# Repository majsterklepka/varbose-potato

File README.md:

# varbose-potato
Digital Voltmeter based on ICL7107

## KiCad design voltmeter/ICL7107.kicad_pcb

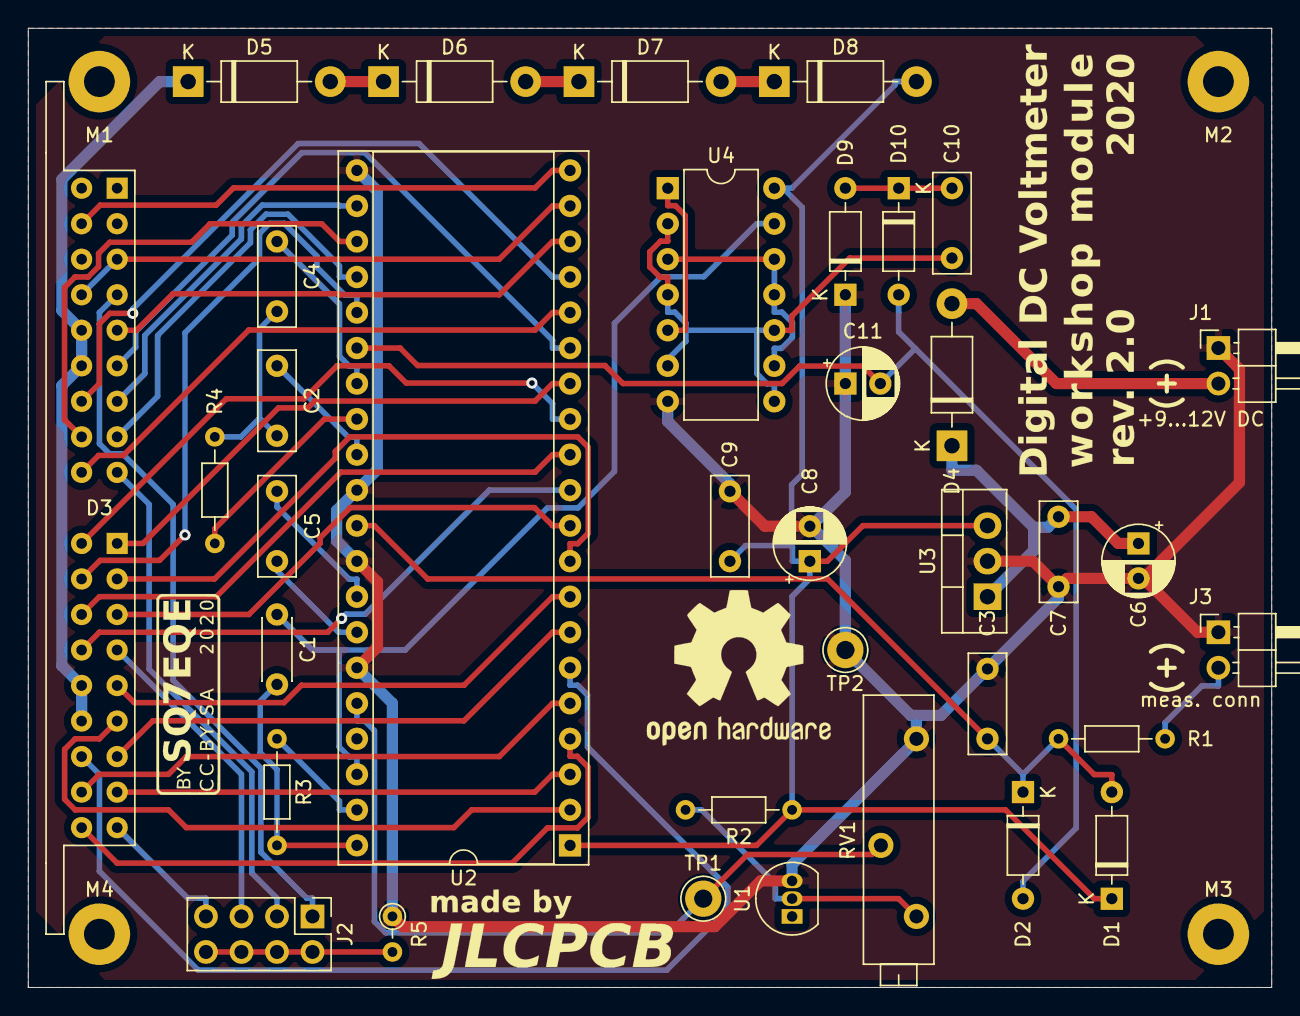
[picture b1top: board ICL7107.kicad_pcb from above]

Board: 2 copper layers, 88.9 x 68.6 mm, 43 parts (0 on the bottom side), 53 nets.

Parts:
C1: 100p; C_Disc_D4.3mm_W1.9mm_P5.00mm
C2, C3, C10: 0.47u; C_Rect_L7.0mm_W2.5mm_P5.00mm
C4: 0.22u; C_Rect_L7.0mm_W2.5mm_P5.00mm
C5: 0.1u; C_Rect_L7.0mm_W2.5mm_P5.00mm
C6, C8: 100u; CP_Radial_D5.0mm_P2.50mm
C7, C9: 100n; C_Rect_L7.0mm_W2.5mm_P5.00mm
C11: 10u; CP_Radial_D5.0mm_P2.50mm
D1, D2: 1N4148; D_DO-35_SOD27_P7.62mm_Horizontal
D3: LED-Display_x4_CA; LED-Display_x4_package
D4, D5, D6, D7, D8: 1N4001; D_DO-41_SOD81_P10.16mm_Horizontal
D9, D10: 1N914; D_DO-35_SOD27_P7.62mm_Horizontal
G1: CC-BY-SA; cc-by-sa
G2: JLCPCB; jlcpcb
J1: +9...12V DC; PinHeader_1x02_P2.54mm_Horizontal
J2: DP conn.; PinHeader_2x04_P2.54mm_Vertical
J3: meas. conn; PinHeader_1x02_P2.54mm_Horizontal
LOGO1: Logo_Open_Hardware_Large; OSHW-Logo2_14.6x12mm_SilkScreen
M1, M2, M3, M4: M2.2; MountingHole_2.2mm_M2_Pad
R1: 1M; R_Axial_DIN0204_L3.6mm_D1.6mm_P7.62mm_Horizontal
R2: 6k8; R_Axial_DIN0204_L3.6mm_D1.6mm_P7.62mm_Horizontal
R3: 100k; R_Axial_DIN0204_L3.6mm_D1.6mm_P7.62mm_Horizontal
R4: 47k; R_Axial_DIN0204_L3.6mm_D1.6mm_P7.62mm_Horizontal
R5: 470R; R_Axial_DIN0204_L3.6mm_D1.6mm_P2.54mm_Vertical
RV1: 20k; Potentiometer_Vishay_43_Horizontal
TP1, TP2: Pin_D1.3mm_L11.0mm
U1: LM285Z-1.2; TO-92_Inline
U2: ICL7107; DIP-40_W15.24mm_Socket
U3: L7805; TO-220-3_Vertical
U4: 4069; DIP-14_W7.62mm

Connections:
+5V: C8.1, C9.1, D1.1, D8.2, R2.1, U2.1, U3.3, U4.14
-5V: C11.2, D2.2, D10.2, U2.26
/DP1: D3.27, J2.7
/DP2: D3.22, J2.5
/DP3: D3.9, J2.3
/DP4: D3.4, J2.1
/IN+: J3.2, R1.2
GND: C3.2, C6.2, C7.2, C8.2, C9.2, C11.1, D9.1, J1.1, J3.1, R5.1, RV1.1, TP2.1, U1.3, U2.21, U2.30, U2.32, U2.35, U3.2, U4.7
unnamed: C1.2, R3.2, U2.40
unnamed: C2.1, U2.29
unnamed: C2.2, C4.2, R4.2
unnamed: C3.1, D1.2, D2.1, R1.1, U2.31
unnamed: C4.1, U2.27
unnamed: C5.1, U2.34
unnamed: C5.2, U2.33
unnamed: C6.1, C7.1, D4.1, U3.1
unnamed: C10.1, D9.2, D10.1
unnamed: C10.2, U4.2, U4.4, U4.6, U4.8, U4.10
unnamed: D3.5, U2.18
unnamed: D3.6, U2.15
unnamed: D3.7, U2.22
unnamed: D3.8, U2.24
unnamed: D3.10, U2.16
unnamed: D3.11, U2.23
unnamed: D3.12, U2.17
unnamed: D3.13, D3.14, D3.31, D3.32, D5.1
unnamed: D3.3, D3.15, U2.19
unnamed: D3.17, U2.20
unnamed: D3.19, U2.14
unnamed: D3.20, U2.9
unnamed: D3.21, U2.10
unnamed: D3.23, U2.8
unnamed: D3.24, U2.2
unnamed: D3.25, U2.7
unnamed: D3.26, U2.3
unnamed: D3.28, U2.4
unnamed: D3.29, U2.5
unnamed: D3.30, U2.6
unnamed: D3.33, U2.11
unnamed: D3.34, U2.12
unnamed: D3.35, U2.25
unnamed: D3.36, U2.13
unnamed: D4.2, J1.2
unnamed: D5.2, D6.1
unnamed: D6.2, D7.1
unnamed: D7.2, D8.1
unnamed: J2.2, J2.4, J2.6, J2.8, R5.2
unnamed: R2.2, RV1.3, U1.2
unnamed: R3.1, U2.39
unnamed: R4.1, U2.28
unnamed: RV1.2, TP1.1, U2.36
unnamed: U4.1, U4.3, U4.5, U4.9, U4.11, U4.12
OSC3: C1.1, U2.38, U4.13

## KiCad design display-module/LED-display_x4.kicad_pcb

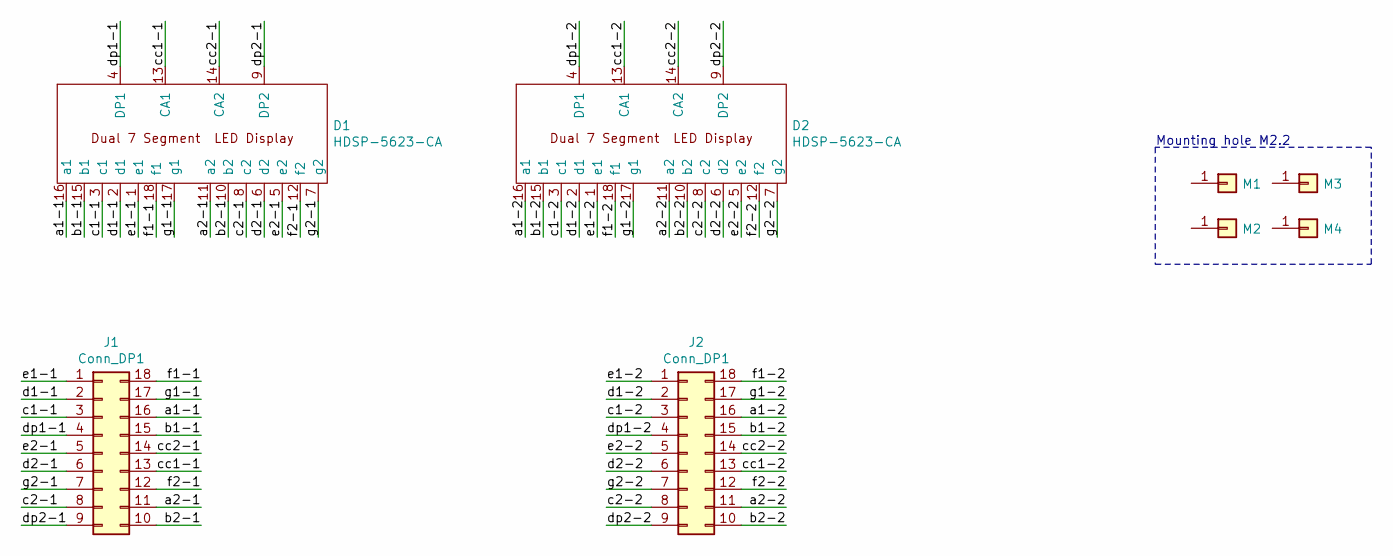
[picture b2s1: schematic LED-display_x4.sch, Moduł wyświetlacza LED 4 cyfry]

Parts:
D1, D2: HDSP-5623-CA; package_led_display_0.56in_dual
J1, J2: Conn_DP1; PinHeader_2x09_P2.54mm_Horizontal
M1, M2, M3, M4: Conn_01x01; MountingHole_2.2mm_M2

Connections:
/a1-1: D1.16 (a1), J1.16
/a1-2: D2.16 (a1), J2.16
/a2-1: D1.11 (a2), J1.11
/a2-2: D2.11 (a2), J2.11
/b1-1: D1.15 (b1), J1.15
/b1-2: D2.15 (b1), J2.15
/b2-1: D1.10 (b2), J1.10
/b2-2: D2.10 (b2), J2.10
/c1-1: D1.3 (c1), J1.3
/c1-2: D2.3 (c1), J2.3
/c2-1: D1.8 (c2), J1.8
/c2-2: D2.8 (c2), J2.8
/cc1-1: D1.13 (CA1), J1.13
/cc1-2: D2.13 (CA1), J2.13
/cc2-1: D1.14 (CA2), J1.14
/cc2-2: D2.14 (CA2), J2.14
/d1-1: D1.2 (d1), J1.2
/d1-2: D2.2 (d1), J2.2
/d2-1: D1.6 (d2), J1.6
/d2-2: D2.6 (d2), J2.6
/dp1-1: D1.4 (DP1), J1.4
/dp1-2: D2.4 (DP1), J2.4
/dp2-1: D1.9 (DP2), J1.9
/dp2-2: D2.9 (DP2), J2.9
/e1-1: D1.1 (e1), J1.1
/e1-2: D2.1 (e1), J2.1
/e2-1: D1.5 (e2), J1.5
/e2-2: D2.5 (e2), J2.5
/f1-1: D1.18 (f1), J1.18
/f1-2: D2.18 (f1), J2.18
/f2-1: D1.12 (f2), J1.12
/f2-2: D2.12 (f2), J2.12
/g1-1: D1.17 (g1), J1.17
/g1-2: D2.17 (g1), J2.17
/g2-1: D1.7 (g2), J1.7
/g2-2: D2.7 (g2), J2.7

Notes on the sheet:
Mounting hole M2.2

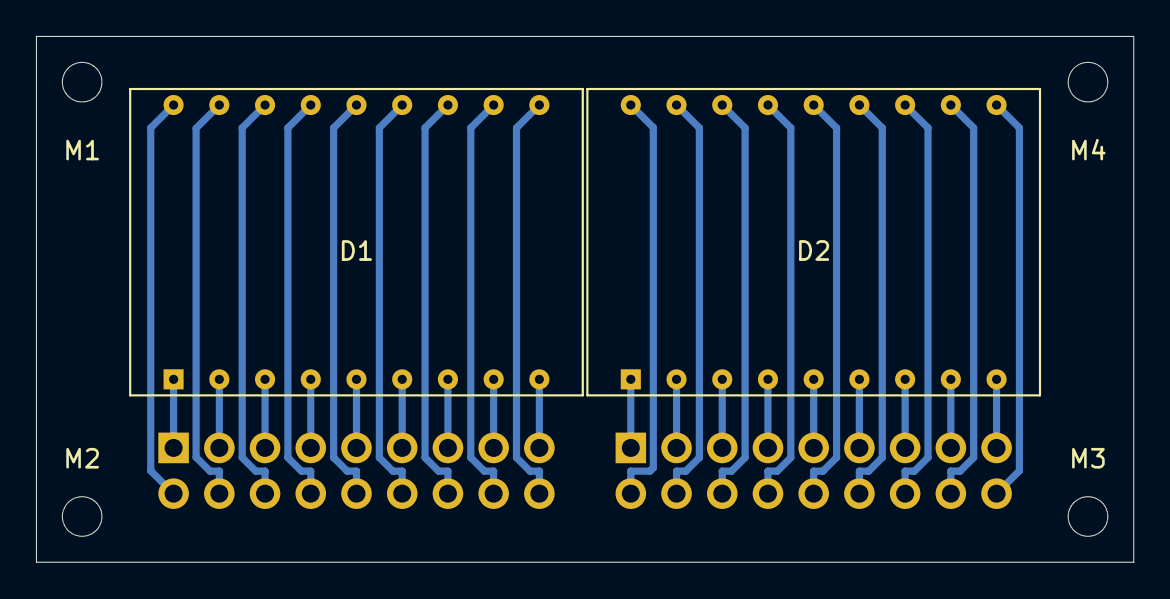
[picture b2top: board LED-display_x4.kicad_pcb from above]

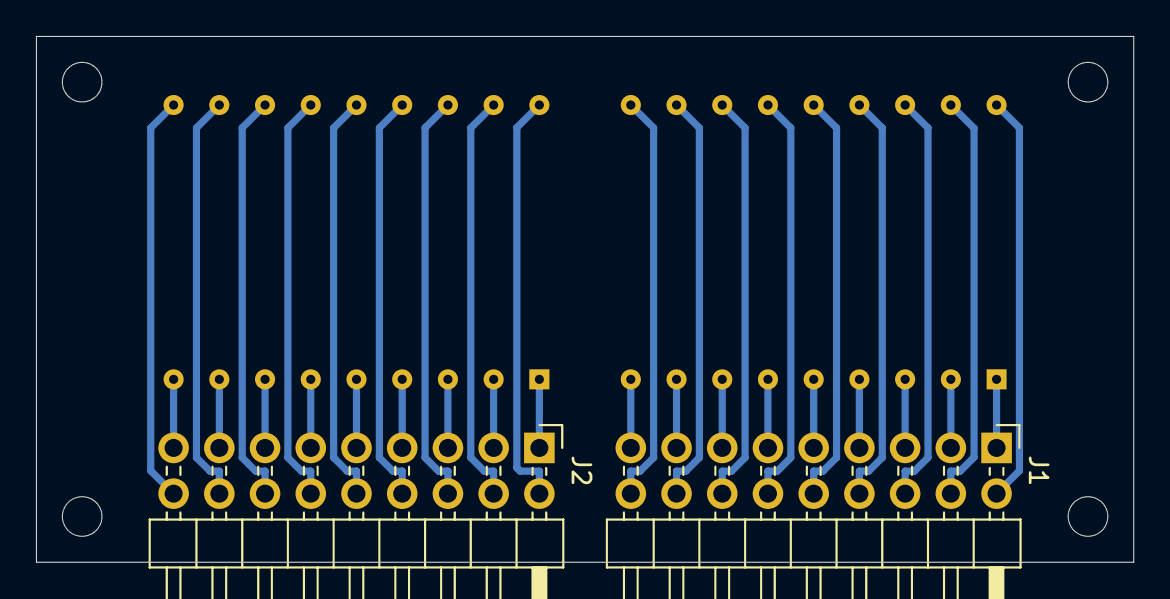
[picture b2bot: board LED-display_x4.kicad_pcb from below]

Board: 2 copper layers, 61.0 x 29.2 mm, 8 parts (2 on the bottom side), 36 nets.

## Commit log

2020-06-01 Rename LICENSE.txt to LICENSE.md
2020-06-01 upload file
2020-06-01 update file
2020-06-02 updated file
2020-06-30 update file
    I make mistake in schematics library & footprint library
    now devices are correct, I divided 7 segment display at
    two separate CA & CC
    bye!
2020-06-30 update
    Zmodyfikowałem schemat i tym samym projekt płytki drukowanej
    usunąłem zbędne rezystory i poprawnie połączyłem dp wyświetlaczy
2020-07-05 update file
    poprawiłem schemat i ponownie wygenerowałem pliki Gerber
    I corrected the diagram and re-generated the Gerber files
2020-07-07 generate BOM list
2020-07-08 BOM list update
2020-07-29 update
    Dziś odebrałem płytki z wytwórni płytek, poprawiłem
    projekt footprintów dla wyświetlaczy LED
    pierwotny projekt był na wcisk, teraz po dodaniu 0.1mm na średnicy
    powinno byc lepiej
2020-07-29 update
    Zmodyfikowałem projekt footprintu dla wyświetlacza LED
    dostosowałem średnicę otworów do średnicy dostępnych wierteł
    ponownie wygenerowałem pliki Gerber
2020-07-29 new uploaded file with schematic diagram
2020-07-31 update
    I have regenerated Gerber files
    I make correction of schematic diagram
2020-07-31 new file
    uploaded new file:
    - with Gerber files
    - with Kicad footprint module
2020-07-31 new file uploaded
    example application of module
    - AC voltmeter
    - DC voltmeter
    all two schematic diagram in PDF file format
2020-07-31 update file
    update file with last changes
2020-08-07 update file
    uaktualniłem footprint(wyświetlacz LED) i ponownie przygotowałem plik zip
2020-08-07 update file
    ponowne wygenerowanie plików Gerber, powód: uaktualniony footprint
2020-08-07 upload modified file

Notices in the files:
display-module/LED-display_x4.kicad_pcb:
CC-BY-SA 4.0
